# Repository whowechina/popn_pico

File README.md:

# Popn Pico - Pop'n Music Style Mini Controller
[点这里可以切换到中文版](README_CN.md)

I've made two generations of Popn Pico. The latest is Popn Pico 2. It's larger than the first generation.

The document here is for the latest generation. The files for the first generation are archived in `Gen1Archive` folder. This is what the first generation looks like.  

Features:
* It uses self-made 40mm dome buttons.
* Full HID light support.
* Command line for configurations.
* All source files open.

Thanks to many respectful guys/companies who made their tools or materials free or open source (KiCad, OnShape, InkScape, Raspberry things).

Special thanks to community projects and developers.
And also these projects:
* RP_Silicon_KiCad: https://github.com/HeadBoffin/RP_Silicon_KiCad
* Type-C: https://github.com/ai03-2725/Type-C.pretty

## About the License
It's CC-NC. So DIY for yourself and for your friend for free, don't make money from it. And plagiarism that doesn’t even dare to mention the original author is not acceptable. Plase note that pooling orders and group buying for raw materials is acceptable. Selling off any leftover components without profit is also acceptable.

If you're interested in buying from me or some kind of commercial use, please contact me (Discord, QQ group, Wechat group or leave your contact in issue section).

## My Discord Invitation
https://discord.gg/M8f2PPQFEA

## My Other Projects
You can check out my other cool projects.

* Popn Pico: https://github.com/whowechina/popn_pico
* IIDX Pico: https://github.com/whowechina/iidx_pico
* IIDX Teeny: https://github.com/whowechina/iidx_teeny
* Chu Pico: https://github.com/whowechina/chu_pico
* Mai Pico: https://github.com/whowechina/mai_pico
* Diva Pico: https://github.com/whowechina/diva_pico
* AIC Pico: https://github.com/whowechina/aic_pico
* Groove Pico: https://github.com/whowechina/groove_pico
* Geki Pico: https://github.com/whowechina/geki_pico
* Musec Pico: https://github.com/whowechina/musec_pico
* Ju Pico: https://github.com/whowechina/ju_pico
* Bishi Pico: https://github.com/whowechina/bishi_pico
* Bishi Pico: https://github.com/whowechina/nos_pico

## **Disclaimer** ##
I made this project in my personal time without any sponsorship. I will continue to improve the project. I have done my best to ensure that everything is accurate and functional, there's always a chance that mistakes may occur. I cannot be held responsible for any loss of your time or money that may result from using this open source project. Thank you for your understanding.

## HOW TO BUILD
### PCB and Components
* Go JLCPCB or any PCB vendor you like, make order with the gerber zip files (latest `Production\PCB\popn_pico2_xxx.zip`), regular FR-4 board, black color, **1.6mm** thickness.
* 1x Rasberry Pico Pi Pico or pin-to-pin compatible clones.  
  https://www.raspberrypi.com/products/raspberry-pi-pico
* 1x USB Type-C socket (918-418K2023S40001 or KH-TYPE-C-16P)
* 27x WS2812B-3528 RGB LEDs.
* 9x WS2812B-4020 RGB LEDs (side facing).
* 6x 0603 0.1uF (0.1~1uF all fine) capacitors.
* 2x 0603 5.1kohm resistors.
* 9x Kailh Choc v2 switches, linear 35-50gf ones are recommended. I personally use Kailh White Rain switches.
* 2x ALPS SKHHLWA010 6\*6\*7mm or compatible tactile switches.  
  https://tech.alpsalpine.com/e/products/detail/SKHHLWA010/

* This is how it looks after soldering.  

* Becareful of 2 pin holes. It's a common oversight to either forget to solder them or to leave air bubbles during the process. To avoid this, solder slowly from one side of the hole, using minimal solder wire and a generous amount of flux.  

### Test the PCB
* You can test the PCB now, put the firmware in.
* LEDs should light up and respond to the button presses.
* Popn Pico should be recognized as a USB HID device, here's the test page.  
  https://whowechina.github.io/iidx_pico/Tools/gamepad_test.html

### 3D Printing
#### Printing parameters  
* PLA or PETG.
* Layer height: 0.2mm
* Wall: >= 3.
* Support: Yes, always, but only on bed and no need for bridges.
* Glue on bed: Yes, it prevents corner warping.
* Files are always in milimeter unit, not inch.

#### Housing Parts
* Base: `Production\3DPrint\popn_pico2_base.stl`. Color is up to you. Support will help the screw holes.
* Middle Support: `Production\3DPrint\popn_pico2_support.stl`, clear transparent.
* Panel: `Production\3DPrint\popn_pico2_panel.3mf`. A multi-color system is highly recommended, so you can choose your favorate colors for each sub-component.

#### 9x Button Seats
* Button Seat: `Production\3DPrint\popn_pico2_button_seat.stl`, white, print upside down.

### Assembly
#### Other components needed
* 9x Chirstmas tree clear plastic balls, 40mm diameter. They come in 2 half-balls, we only need the shorter one.  
  https://www.amazon.com/Plastic-Fillable-Ornaments-Acrylic-Christmas/dp/B09ZTSGL28/
* 8x **M3\*12mm screws** for fixing the housing parts together.
* 8x silicone anti-slip pads (12mm diameter) for the bottom.
* Clear soft/flexible glue or UV curing glue. WARNING: Avoid using any cyanoacrylate-based glue, such as 502. Any glue with a similar smell should also be avoided, as they will leave white smoke marks on the acrylic.

#### Steps
1. We'll make 9 dome button caps first. Just glue the shorter half of the clear plastic ball onto the button seat use the glue mentioned earlier.  
   
2. Install 9 dome button caps onto the switches.
5. Put the PCB into the base part, and then put on the middle frame, and lastly put on the panel. Tighten them using M3 screws. Put anti-slip pads on the bottom, right on top of the screws.

#### Caution
* Each 3D printer and filament has its own tolerance. If you find the stem holes on the button are too tight, use some needle or knife to enlarge them a little bit.
* Screws are easy to break the 3D printed parts. So don't screw them too fast or too tight. When you notice the resistance suddenly increases, stop screwing.

### Firmware
* UF2 file is in `Production\Firmware` folder.
* For the new build, hold the BOOTSEL button while connect the USB to a PC, there will be a disk named "RPI-RP2" showed up. Drag the UF2 firmware binary file into it. That's it. There's a small hole at the bottom side of the Popn Pico 2, it is facing right to the BOOTSEL button.
* If it's already running Popn Pico 2 firmware, you can either use "update" in command line or hold down more than 4 buttons while connecting to USB to enter update mode.
* To access the command line, you can use this Web Serial Terminal to connect to the command line port of the controller. (Note: "?" is for help)  
  https://whowechina.github.io/iidx_pico/Tools/cli_tool.html

### Usage
* It's very simple. Just plug and play.

### Bonus - Popn Visa Card Holder

* Popn Visa card holder is a bonus design for Popn Pico. It can be used to hold your credit card sized arcade cards.
* Print the base and the panel, assign different color for the pattern and text on the panel. `_insert` means it's the heat-set insert version. `_flat` means it's for flat head (countersunk) screws. Transparent material is recommended.
* If you choose the `_insert` version, use 4x M1.2\*1.5mm\*2mm (thread size\*length\*diameter) heat-set inserts on base part.
* 4x M1.2\*3mm screws to fix the panel and the base together. If you choose the `_flat` version, use M1.2\*3mm flat head screws.

## CAD Source File
I'm using OnShape free subscription. It's powerful but it can't archive original designs to local, so I can only share the link here. STL/DXF/DWG files are exported from this online document.  
  https://cad.onshape.com/documents/fcfa3f71e200593febd1451f/w/3452f2d9fccae7d99b53d89a/e/55b4cd1b258679099c74739b

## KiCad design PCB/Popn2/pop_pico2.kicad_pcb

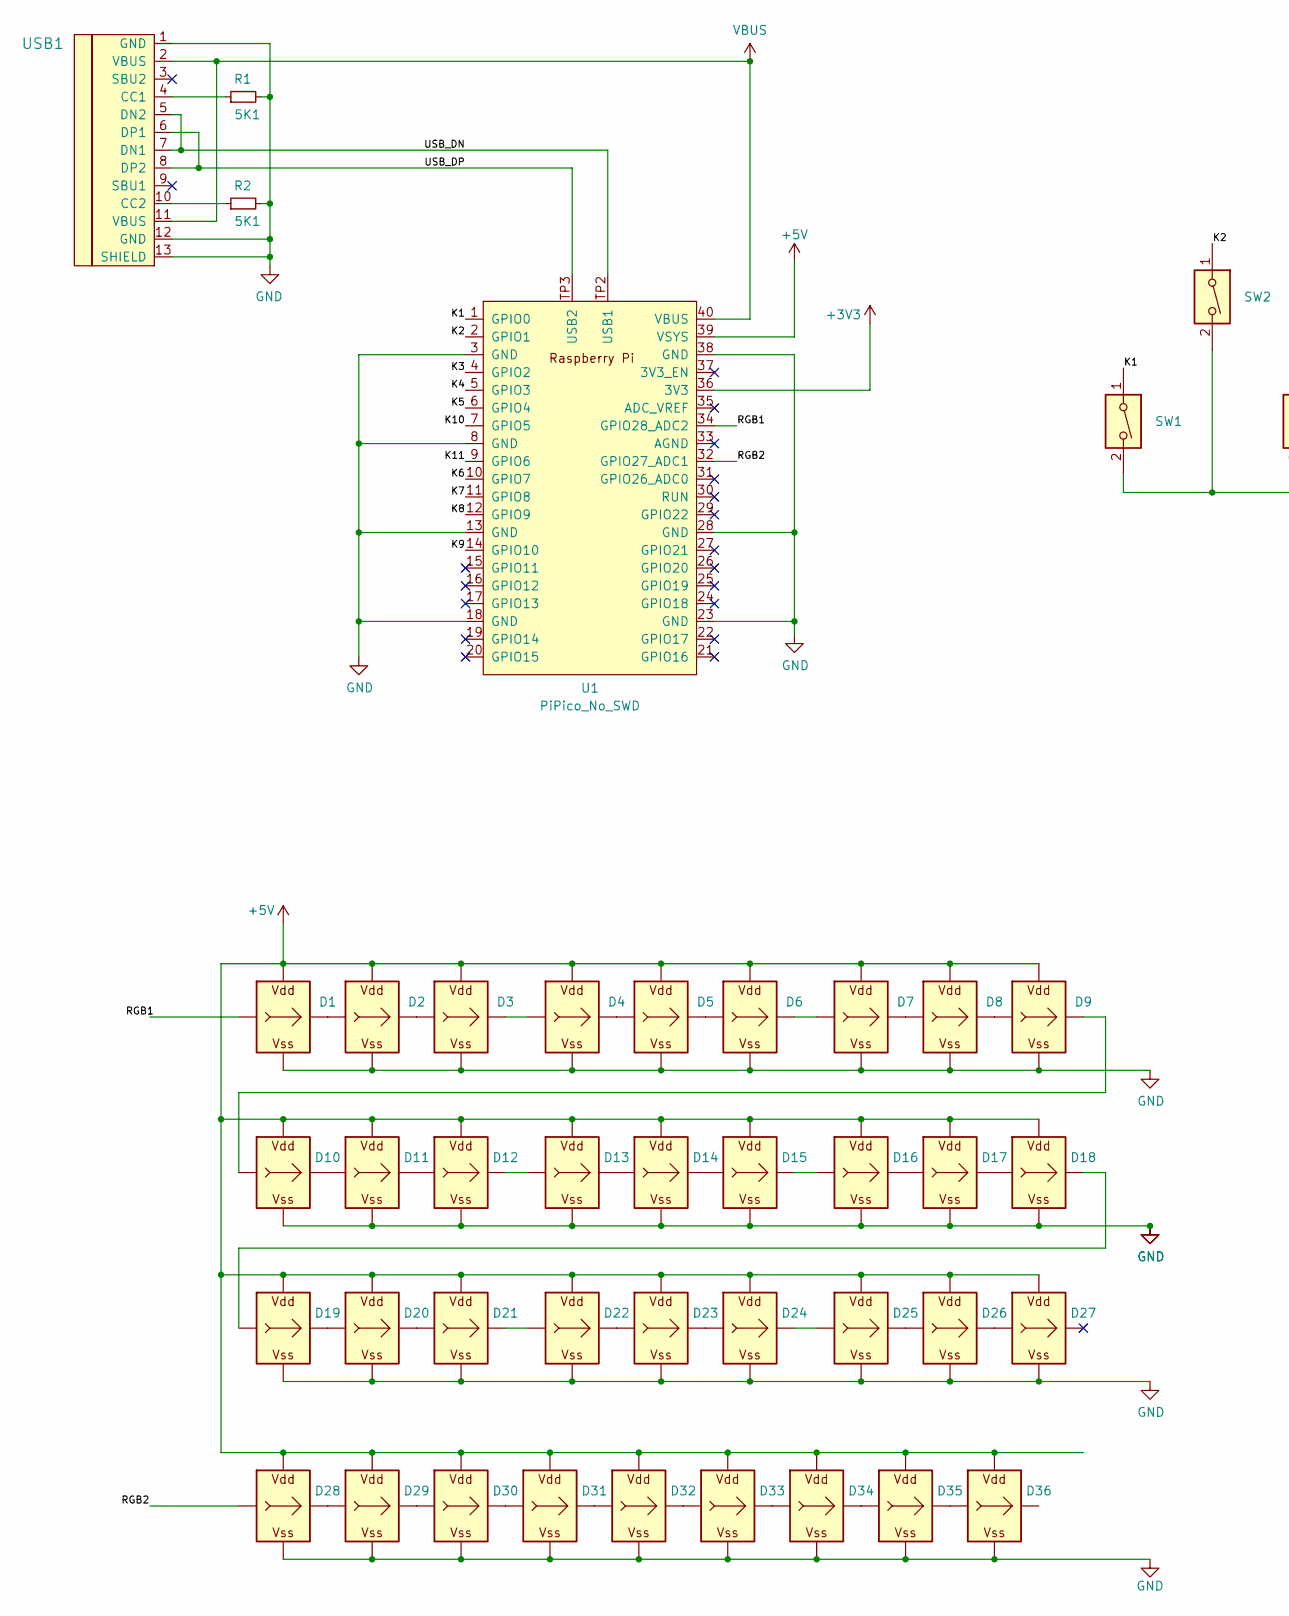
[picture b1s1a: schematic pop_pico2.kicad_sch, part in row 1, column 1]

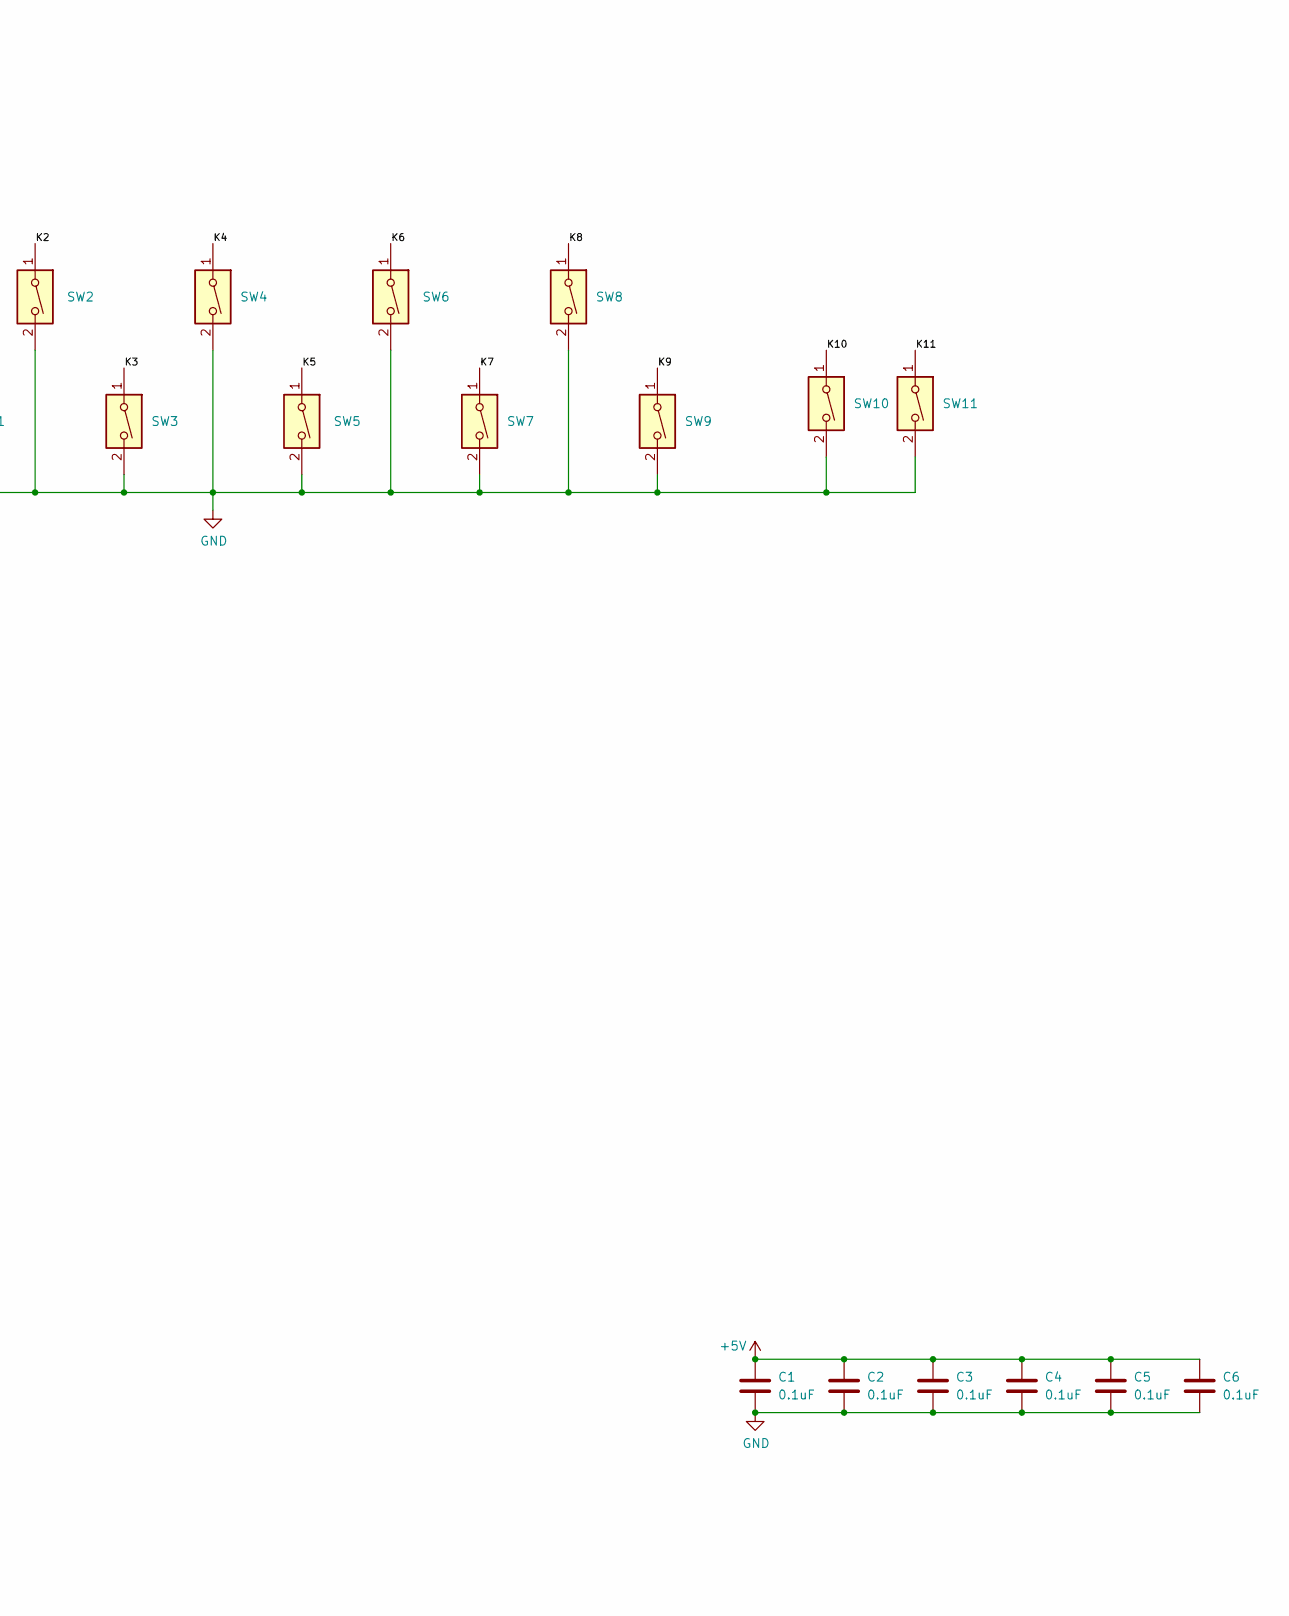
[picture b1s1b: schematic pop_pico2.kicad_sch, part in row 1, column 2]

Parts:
C1, C2, C3, C4, C5, C6: 0.1uF; C_0603_1608Metric_Pad1.08x0.95mm_HandSolder
D1, D2, D3, D4, D5, D6, D7, D8, D9, D10, D11, D12, D13, D14, D15, D16, D17, D18, D19, D20, D21, D22, D23, D24, D25, D26, D27: WS2812B_Unified; WS2812B-2835
D28, D29, D30, D31, D32, D33, D34, D35, D36: WS2812B_Unified; WS2812B-4020
R1, R2: 5K1; R_0603_1608Metric_Pad0.98x0.95mm_HandSolder; LCSC C23186
SW1, SW2, SW3, SW4, SW5, SW6, SW7, SW8, SW9: SW_DIP_x01; SW_Choc_V1V2_Cherry_MX_LED
SW10, SW11: SW_DIP_x01; Omron_B3F-315x_Angled
U1: PiPico_No_SWD; RPi_Pico_SMD_Pins_No_SWD
USB1: U262-161N-4BVC11; HRO-TYPE-C-31-M-12-Assembly; LCSC C319148

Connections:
+3V3: U1.36 (3V3)
+5V: C1.1, C2.1, C3.1, C4.1, C5.1, C6.1, D1.V (VDD), D2.V (VDD), D3.V (VDD), D4.V (VDD), D5.V (VDD), D6.V (VDD), D7.V (VDD), D8.V (VDD), D9.V (VDD), D10.V (VDD), D11.V (VDD), D12.V (VDD), D13.V (VDD), D14.V (VDD), D15.V (VDD), D16.V (VDD), D17.V (VDD), D18.V (VDD), D19.V (VDD), D20.V (VDD), D21.V (VDD), D22.V (VDD), D23.V (VDD), D24.V (VDD), D25.V (VDD), D26.V (VDD), D27.V (VDD), D28.V (VDD), D29.V (VDD), D30.V (VDD), D31.V (VDD), D32.V (VDD), D33.V (VDD), D34.V (VDD), D35.V (VDD), D36.V (VDD), U1.39 (VSYS)
/K1: SW1.1, U1.1 (GPIO0)
/K2: SW2.1, U1.2 (GPIO1)
/K3: SW3.1, U1.4 (GPIO2)
/K4: SW4.1, U1.5 (GPIO3)
/K5: SW5.1, U1.6 (GPIO4)
/K6: SW6.1, U1.10 (GPIO7)
/K7: SW7.1, U1.11 (GPIO8)
/K8: SW8.1, U1.12 (GPIO9)
/K9: SW9.1, U1.14 (GPIO10)
/K10: SW10.1, U1.7 (GPIO5)
/K11: SW11.1, U1.9 (GPIO6)
/RGB1: D1.I (In), U1.34 (GPIO28_ADC2)
/RGB2: D28.I (In), U1.32 (GPIO27_ADC1)
/USB_DN: U1.TP2 (USB1), USB1.5 (DN2), USB1.7 (DN1)
/USB_DP: U1.TP3 (USB2), USB1.6 (DP1), USB1.8 (DP2)
GND: C1.2, C2.2, C3.2, C4.2, C5.2, C6.2, D1.G (VSS), D2.G (VSS), D3.G (VSS), D4.G (VSS), D5.G (VSS), D6.G (VSS), D7.G (VSS), D8.G (VSS), D9.G (VSS), D10.G (VSS), D11.G (VSS), D12.G (VSS), D13.G (VSS), D14.G (VSS), D15.G (VSS), D16.G (VSS), D17.G (VSS), D18.G (VSS), D19.G (VSS), D20.G (VSS), D21.G (VSS), D22.G (VSS), D23.G (VSS), D24.G (VSS), D25.G (VSS), D26.G (VSS), D27.G (VSS), D28.G (VSS), D29.G (VSS), D30.G (VSS), D31.G (VSS), D32.G (VSS), D33.G (VSS), D34.G (VSS), D35.G (VSS), D36.G (VSS), R1.2, R2.2, SW1.2, SW2.2, SW3.2, SW4.2, SW5.2, SW6.2, SW7.2, SW8.2, SW9.2, SW10.2, SW11.2, U1.3 (GND), U1.8 (GND), U1.13 (GND), U1.18 (GND), U1.23 (GND), U1.28 (GND), U1.38 (GND), USB1.1 (GND), USB1.12 (GND), USB1.13 (SHIELD)
unnamed: D1.O (Out), D2.I (In)
unnamed: D2.O (Out), D3.I (In)
unnamed: D3.O (Out), D4.I (In)
unnamed: D4.O (Out), D5.I (In)
unnamed: D5.O (Out), D6.I (In)
unnamed: D6.O (Out), D7.I (In)
unnamed: D7.O (Out), D8.I (In)
unnamed: D8.O (Out), D9.I (In)
unnamed: D9.O (Out), D10.I (In)
unnamed: D10.O (Out), D11.I (In)
unnamed: D11.O (Out), D12.I (In)
unnamed: D12.O (Out), D13.I (In)
unnamed: D13.O (Out), D14.I (In)
unnamed: D14.O (Out), D15.I (In)
unnamed: D15.O (Out), D16.I (In)
unnamed: D16.O (Out), D17.I (In)
unnamed: D17.O (Out), D18.I (In)
unnamed: D18.O (Out), D19.I (In)
unnamed: D19.O (Out), D20.I (In)
unnamed: D20.O (Out), D21.I (In)
unnamed: D21.O (Out), D22.I (In)
unnamed: D22.O (Out), D23.I (In)
unnamed: D23.O (Out), D24.I (In)
unnamed: D24.O (Out), D25.I (In)
unnamed: D25.O (Out), D26.I (In)
unnamed: D26.O (Out), D27.I (In)
unnamed: D28.O (Out), D29.I (In)
unnamed: D29.O (Out), D30.I (In)
unnamed: D30.O (Out), D31.I (In)
unnamed: D31.O (Out), D32.I (In)
unnamed: D32.O (Out), D33.I (In)
unnamed: D33.O (Out), D34.I (In)
unnamed: D34.O (Out), D35.I (In)
unnamed: D35.O (Out), D36.I (In)
unnamed: R1.1, USB1.4 (CC1)
unnamed: R2.1, USB1.10 (CC2)
VBUS: U1.40 (VBUS), USB1.2 (VBUS), USB1.11 (VBUS)

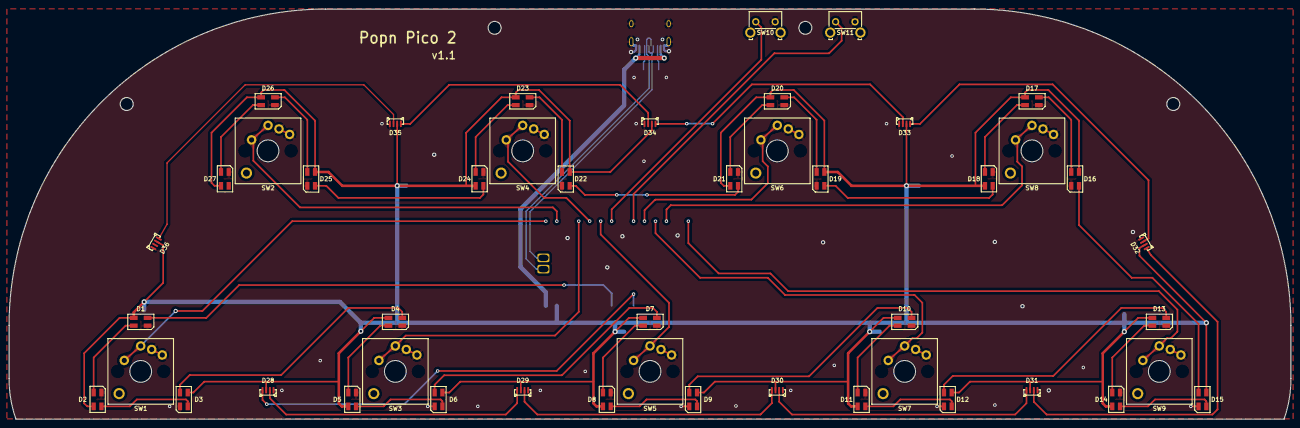
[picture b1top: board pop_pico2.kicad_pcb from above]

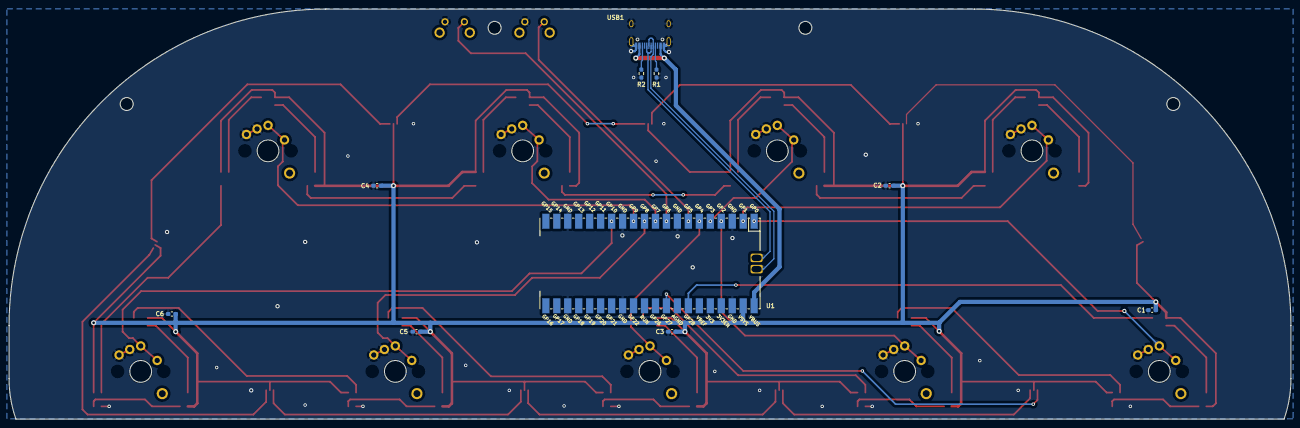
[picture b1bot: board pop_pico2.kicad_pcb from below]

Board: 2 copper layers, 297.0 x 95.0 mm, 57 parts (10 on the bottom side), 54 nets.

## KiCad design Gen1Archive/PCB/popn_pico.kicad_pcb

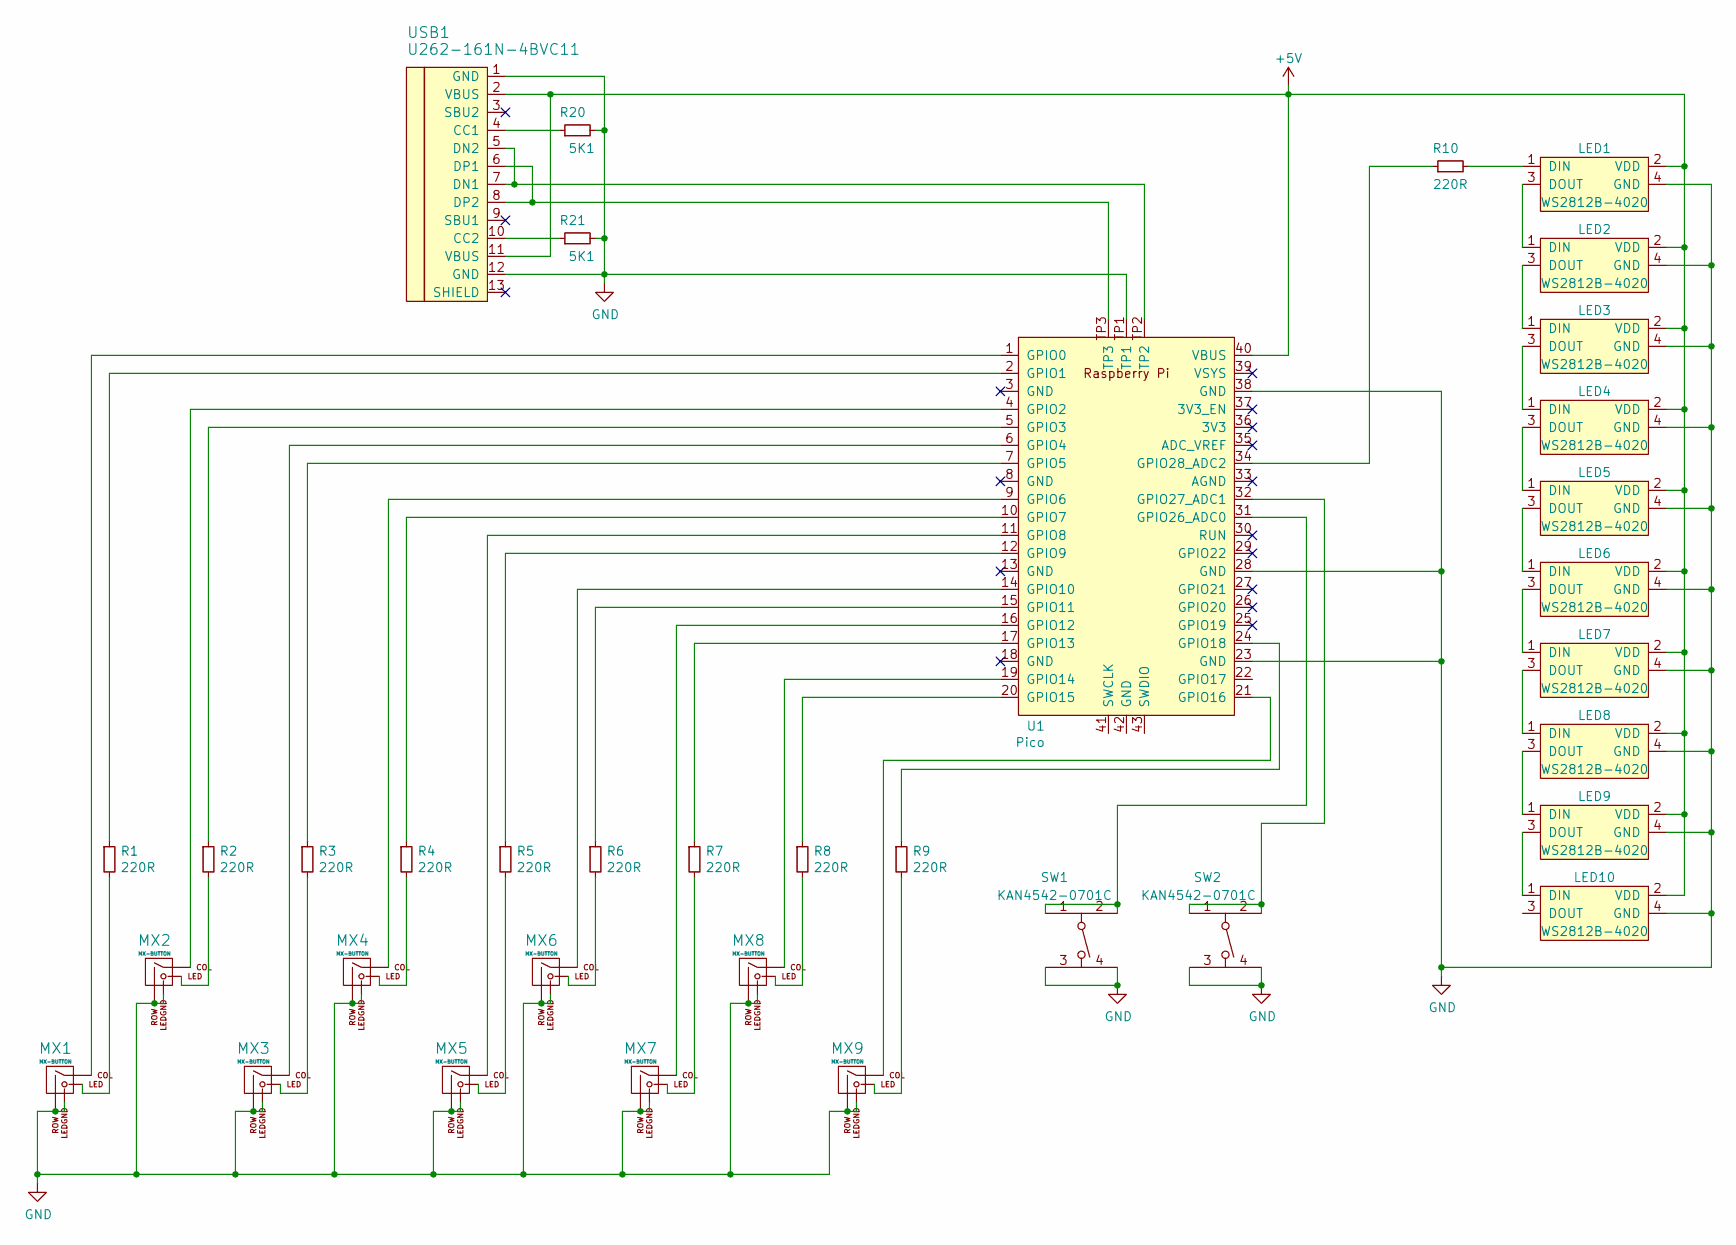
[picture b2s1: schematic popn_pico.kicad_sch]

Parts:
LED1, LED2, LED3, LED4, LED5, LED6, LED7, LED8, LED9, LED10: WS2812B-4020
MX1: MX-BUTTON; MXOnly-Popn_Button-Hotswap-LED; LCSC C440444
MX2, MX3, MX4, MX5: MX-BUTTON; MXOnly-Popn_Button-Hotswap-LED; LCSC C26545
MX6, MX7, MX8, MX9: MX-BUTTON; MXOnly-Popn_Button-Hotswap-LED; LCSC C440441
R1, R2, R3, R4, R5, R6, R7, R8, R9, R10: 220R; R_0603_1608Metric; LCSC C22962
R20, R21: 5K1; R_0603_1608Metric; LCSC C23186
SW1, SW2: KAN4542-0701C; LCSC C231726
U1: Pico; RPi_Pico_SMD
USB1: U262-161N-4BVC11; HRO-TYPE-C-31-M-12-Assembly; LCSC C319148

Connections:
+5V: LED1.2 (VDD), LED2.2 (VDD), LED3.2 (VDD), LED4.2 (VDD), LED5.2 (VDD), LED6.2 (VDD), LED7.2 (VDD), LED8.2 (VDD), LED9.2 (VDD), LED10.2 (VDD), U1.40 (VBUS), USB1.2 (VBUS), USB1.11 (VBUS)
GND: LED1.4 (GND), LED2.4 (GND), LED3.4 (GND), LED4.4 (GND), LED5.4 (GND), LED6.4 (GND), LED7.4 (GND), LED8.4 (GND), LED9.4 (GND), LED10.4 (GND), MX1.2 (ROW), MX1.4 (LEDGND), MX2.2 (ROW), MX2.4 (LEDGND), MX3.2 (ROW), MX3.4 (LEDGND), MX4.2 (ROW), MX4.4 (LEDGND), MX5.2 (ROW), MX5.4 (LEDGND), MX6.2 (ROW), MX6.4 (LEDGND), MX7.2 (ROW), MX7.4 (LEDGND), MX8.2 (ROW), MX8.4 (LEDGND), MX9.2 (ROW), MX9.4 (LEDGND), R20.2, R21.2, SW1.3, SW1.4, SW2.3, SW2.4, U1.23 (GND), U1.28 (GND), U1.38 (GND), U1.TP1, USB1.1 (GND), USB1.12 (GND)
unnamed: LED1.1 (DIN), R10.2
unnamed: LED1.3 (DOUT), LED2.1 (DIN)
unnamed: LED2.3 (DOUT), LED3.1 (DIN)
unnamed: LED3.3 (DOUT), LED4.1 (DIN)
unnamed: LED4.3 (DOUT), LED5.1 (DIN)
unnamed: LED5.3 (DOUT), LED6.1 (DIN)
unnamed: LED6.3 (DOUT), LED7.1 (DIN)
unnamed: LED7.3 (DOUT), LED8.1 (DIN)
unnamed: LED8.3 (DOUT), LED9.1 (DIN)
unnamed: LED9.3 (DOUT), LED10.1 (DIN)
unnamed: MX1.1 (COL), U1.1 (GPIO0)
unnamed: MX1.3 (LED), R1.2
unnamed: MX2.1 (COL), U1.4 (GPIO2)
unnamed: MX2.3 (LED), R2.2
unnamed: MX3.1 (COL), U1.6 (GPIO4)
unnamed: MX3.3 (LED), R3.2
unnamed: MX4.1 (COL), U1.9 (GPIO6)
unnamed: MX4.3 (LED), R4.2
unnamed: MX5.1 (COL), U1.11 (GPIO8)
unnamed: MX5.3 (LED), R5.2
unnamed: MX6.1 (COL), U1.14 (GPIO10)
unnamed: MX6.3 (LED), R6.2
unnamed: MX7.1 (COL), U1.16 (GPIO12)
unnamed: MX7.3 (LED), R7.2
unnamed: MX8.1 (COL), U1.19 (GPIO14)
unnamed: MX8.3 (LED), R8.2
unnamed: MX9.1 (COL), U1.21 (GPIO16)
unnamed: MX9.3 (LED), R9.2
unnamed: R1.1, U1.2 (GPIO1)
unnamed: R2.1, U1.5 (GPIO3)
unnamed: R3.1, U1.7 (GPIO5)
unnamed: R4.1, U1.10 (GPIO7)
unnamed: R5.1, U1.12 (GPIO9)
unnamed: R6.1, U1.15 (GPIO11)
unnamed: R7.1, U1.17 (GPIO13)
unnamed: R8.1, U1.20 (GPIO15)
unnamed: R10.1, U1.34 (GPIO28_ADC2)
unnamed: R20.1, USB1.4 (CC1)
unnamed: R21.1, USB1.10 (CC2)
unnamed: SW1.1, SW1.2, U1.31 (GPIO26_ADC0)
unnamed: SW2.1, SW2.2, U1.32 (GPIO27_ADC1)
unnamed: R9.1, U1.24 (GPIO18)
unnamed: U1.TP2, USB1.5 (DN2), USB1.7 (DN1)
unnamed: U1.TP3, USB1.6 (DP1), USB1.8 (DP2)

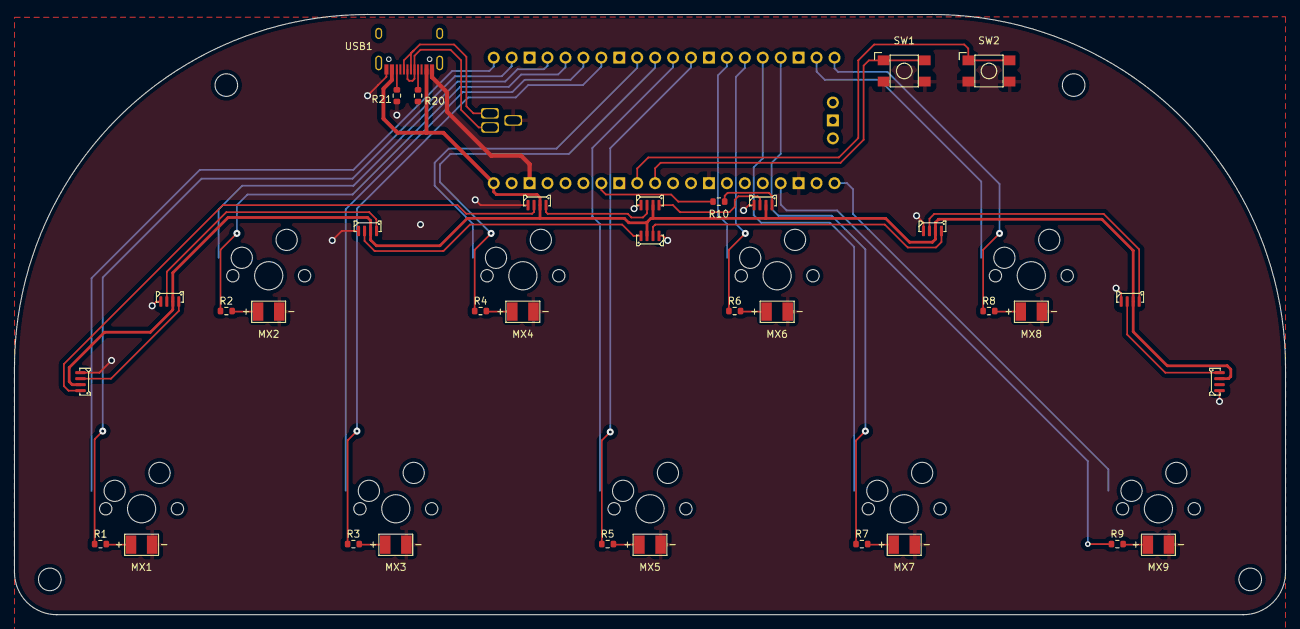
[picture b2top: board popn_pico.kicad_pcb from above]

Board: 2 copper layers, 180.0 x 85.0 mm, 35 parts (1 on the bottom side), 46 nets.

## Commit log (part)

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2022-08-21 Update license
2022-08-21 PCB project and schematics draft
2022-08-22 Update PCB with libs and 3d models
2022-08-28 Finished layout
2022-08-28 Woking on plate
2022-08-29 First PCB production
2022-09-01 Plate go manufacture
2022-09-03 Fixed PCB bug (LED 5v and GND swapped)
2022-09-04 Firmware first commit
    Button and button leds working, no RGB lights, no debouncing.
2022-09-04 Firmware debounce working.
2022-09-04 Start work on case, just main body yet
2022-09-05 Case created with OpenSCAD
2022-09-06 RGB lights working.
2022-09-07 RGB rainbow effect working
2022-09-08 HID logo and rainbow effects both working.
2022-09-08 Minor refactoring
2022-09-10 Case done (and added the missing USB-C slot)
2022-09-11 Better gamma curve
2022-09-12 README ready
2022-09-12 Some fix in README
2022-09-12 Update README with videos
2022-09-12 Attempt to fix video in README
2022-09-12 Limit video width
2022-09-12 Put firmware in production folder
2022-09-12 Remove emails from src
2022-09-13 Screw spacer STL file and some updates to README
2022-09-13 Fix README markdown issues.
2022-10-04 3D printed button option
2022-10-04 Fixed Logo RGB mapping
2022-10-04 Updated main image with printed buttons
2022-10-05 More accurate keycap socket
2022-10-06 Update resin 3d print info
2022-10-06 Minor format fix in README
2022-10-06 Fix README format issue again, I hate that.
2022-10-15 Finetune some case details (USB and Pico)
2022-10-15 Finetune the pcb spacer model
2022-10-21 Update chitubox supports
2023-01-02 LED fade out effects
2023-01-28 LED9 pin changed to support PWM, UF2 firmware updated too
2023-01-28 Update document for PCB modification
2023-01-29 Firmware moved to a separate repo
2023-01-29 Update firmware binary
2023-03-11 Fixed missing screw holes
2023-10-14 Crossreference to other projects
2024-10-02 Cross-reference and license part update
2024-10-18 Cross-reference and Discord invitation
2024-12-04 Archive Gen 1 Files
2024-12-04 Gen2 PCB begins
2024-12-04 Firmware source is back
2024-12-08 Firmware kinda works
2024-12-08 PCB v1.0
2024-12-10 Theme color with fixed hue code
2024-12-15 HID light works
2024-12-17 Main picture of popn pico 2
2025-01-04 Better polling rate
2025-01-06 Guide is ready
2025-01-06 Minor format fixes
2025-01-14 Optimize switch footprints
2025-02-18 Fix file naming
2025-04-04 Cross-reference to Nos Pico
2025-12-25 Smaller pads
2026-02-24 Add periodic hid report
2026-06-08 Popn Visa card holder
2026-06-08 Reduce the risk of panel bend
